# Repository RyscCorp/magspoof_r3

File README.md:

# Magspoof R3
[Rysc Corp](https://ryscc.com)

The [Magspoof R3](https://ryscc.com/products/magspoof) is based on the following prior works:

* https://github.com/samyk/magspoof
* https://github.com/salmg/MagSpoofPI

## Hardware Changes
* Integrated PCB coil
* Coin cell battery
* On/Off switch
* Programming header

## Firmware Changes
* Removed arduino dependencies
* Source code simplification
* Variable swipe speed and track playback speed (improved read reliability)

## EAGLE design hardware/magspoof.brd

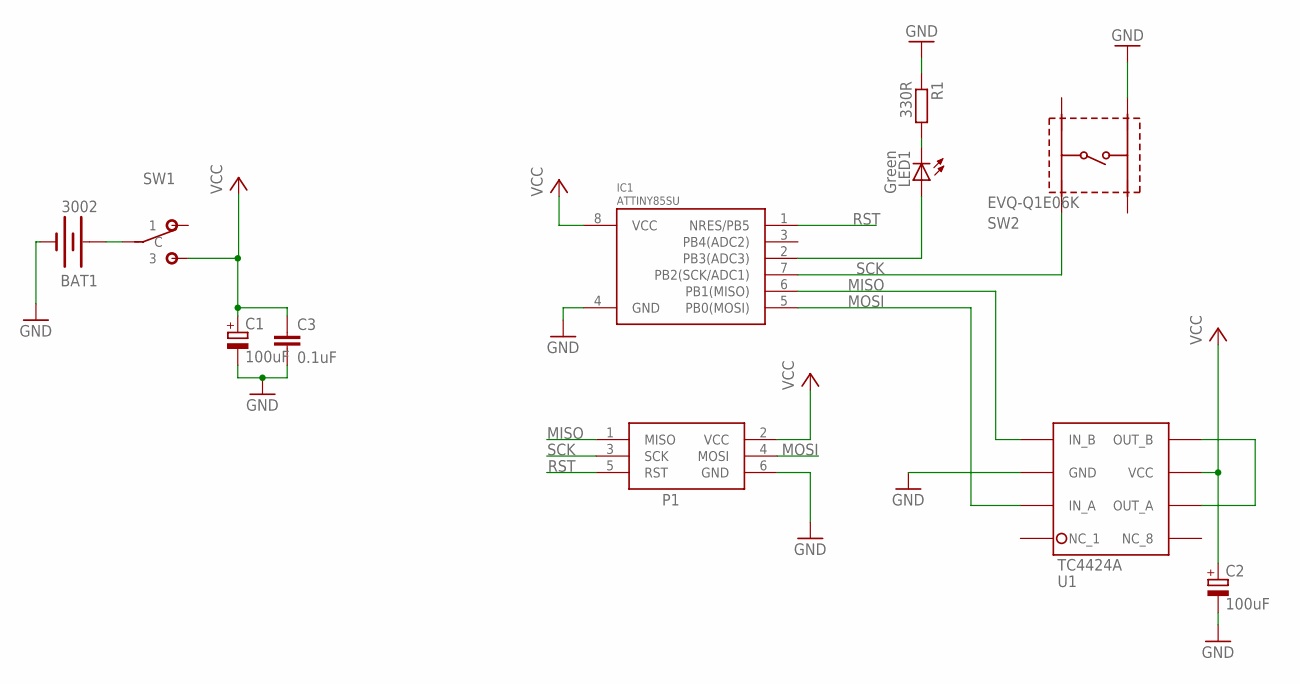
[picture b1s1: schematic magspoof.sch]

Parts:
BAT1: 3002; BATTCON_20MM
C1, C2: 100uF; C1411
C3: 0.1uF; C0603
IC1: ATTINY85SU; ATTINY85
LED1: Green; CHIPLED_0805
P1: AVRISP-6; AVRISP
R1: 330R; R0603
SW1: JS102011; JS102011SAQN
SW2: EVQ-Q1E06K; EVQQ1
U1: TC4424A; 8-SOIC

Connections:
ANTENNA: U1.5 (OUT_B), U1.7 (OUT_A)
GND: BAT1.-, C1.P$2 (-), C2.P$2 (-), C3.2, IC1.4 (GND), P1.6 (GND), R1.1, SW2.D, U1.3 (GND)
MISO: IC1.6 (PB1(MISO)), P1.1 (MISO), U1.4 (IN_B)
MOSI: IC1.5 (PB0(MOSI)), P1.4 (MOSI), U1.2 (IN_A)
unnamed: BAT1.+2 (+), SW1.P$2 (C)
unnamed: IC1.2 (PB3(ADC3)), LED1.A
unnamed: LED1.C, R1.2
RST: IC1.1 (NRES/PB5), P1.5 (RST)
SCK: IC1.7 (PB2(SCK/ADC1)), P1.3 (SCK), SW2.A
VCC: C1.P$1 (+), C2.P$1 (+), C3.1, IC1.8 (VCC), P1.2 (VCC), SW1.P$3 (3), U1.6 (VCC)

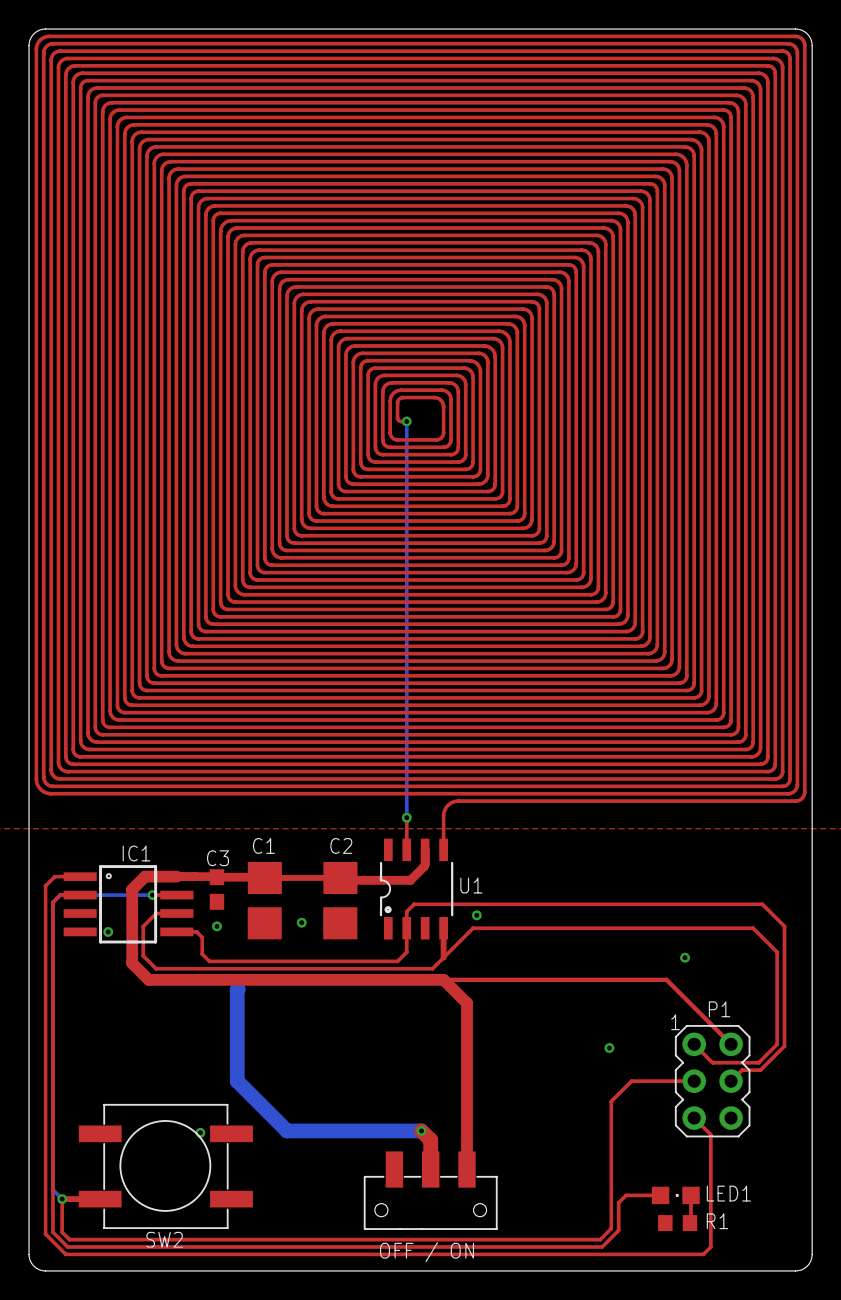
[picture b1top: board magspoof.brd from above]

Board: 2 copper layers, 54.0 x 85.6 mm, 11 parts (1 on the bottom side), 10 nets.

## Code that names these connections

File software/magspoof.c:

/*
 * MagSpoof - "wireless" magnetic stripe/credit card emulator
 *
 * Original by Samy Kamkar
 * MagSpoofPI by Salvador Mendoza
 *
 * http://samy.pl/magspoof
 * https://github.com/salmg/MagSpoofPI
 * https://netxing.wordpress.com/2016/08/27/magspoofpi/
 *
 */


#include <avr/io.h>
#include <util/delay.h>
#include <avr/interrupt.h>
#include <avr/sleep.h>

                            // min 5 IPS, max 50 IPS
#define SWIPE_SPEED   10    // inches per second

#define bool uint8_t
#define HIGH 1
#define LOW 0

#define interrupts() sei()
#define no_interrupts() cli()

/*
#define SINGLE_POLE   // only drive one side of the coil
                      // as described in http://www.idogendel.com/en/archives/507
*/

#define COIL_A PB0
#define COIL_B PB1
#define BUTTON_PIN PB2
#define LED_PIN PB3 
   
// I/O macros
#define PIN_HIGH(pin)   PORTB |= (HIGH << pin)
#define PIN_LOW(pin)    PORTB &= ~(HIGH << pin)
#define PINREAD(pin)    PINB & (HIGH << pin)

const uint16_t leading_zeros[3] = { 10, 20, 10 };
const uint16_t trailing_zeros[3] = { 10, 10, 10 };
const uint8_t track_density[3] = { 210, 75, 210 }; // bits per inch for each track
const uint8_t track_sublen[] = { 32, 48, 48 };
const uint8_t track_bitlen[] = { 7, 5, 5 };

uint32_t track_period_us[3];  // bit period of each track in microseconds
                              // initialized in calc_track_periods()

typedef struct {
  char *tracks[3];  // track data
} card;

// your magstripe card tracks go here
const card test_card = {
  {
    "%B4444444444444444^ABE/LINCOLN^291110100000931?",
    ";4444444444444444=29111010000093100000?",
    0
  },
};

void calc_track_periods()
{
  for (int i = 0; i < 3; i++)
    track_period_us[i] = (uint32_t) (1e6 / (SWIPE_SPEED * track_density[i]));
}

void static inline burn_cycles(uint32_t cycles)
{
  while (cycles > 0) {
    __asm__ volatile ("nop");
    cycles--;
  }
}

void static inline delay_us(uint32_t us)
{
  // obtained divisor of 20 by checking bit period with scope
  // assume loop in burn_cycles requires 20 clock cycles
  uint32_t cycles = (us * (F_CPU / 1000000)) / 20;
  burn_cycles(cycles);
}

void set_pin(uint8_t pin, bool state){
  if (state) {
    PORTB |= (1 << pin); // high
  }
  else {
    PORTB &= ~(1 << pin); // low
  }
}

void blink(int times)
{
  int i;
  for (i = 0; i < times; i++) {
    PIN_HIGH(LED_PIN);
    _delay_ms(200);
    PIN_LOW(LED_PIN);
    _delay_ms(200);
   } 
}

void setup_io()
{
  no_interrupts();

  DDRB |= (1 << COIL_A); // output
  DDRB |= (1 << COIL_B); // output
  DDRB |= (1 << LED_PIN); // output
  // DDRB = 0 by default so

  // BUTTON_PIN configured as input
  PORTB |= (1<<BUTTON_PIN); // set pull-up 
}

void await_button_press()
{
  while (PINREAD(BUTTON_PIN)) // button pin is high when not pressed
    _delay_ms(100);
}

static bool f2f_pole; // used to track signal state during playback (F2F encoding)

static inline void invert_coil_pole()
{
  f2f_pole ^= 1;
  set_pin(COIL_A, f2f_pole);
#ifndef SINGLE_POLE
  set_pin(COIL_B, !f2f_pole);
#endif
}

void f2f_play_bit(bool bit, uint32_t period_us)
{
  // play F2F encoded bit
  // see http://www.edn.com/Home/PrintView?contentItemId=4426351
  const uint32_t half_period = period_us / 2;
  // invert magnetic pole at start of period
  invert_coil_pole();

  delay_us(half_period);

  // at half period, determine whether to invert pole
  if (bit)
    invert_coil_pole();

  delay_us(half_period);
}

void play_zeros(uint8_t n, uint32_t period_us)
{
  for (int i = 0; i < n; i++)
    f2f_play_bit(0, period_us); 
}

void play_byte(
  uint8_t byte, 
  uint8_t n_bits, 
  uint32_t period_us,
  uint8_t *lrc
)
{
    bool parity = 1;
    for (int i = 0; i < n_bits; i++) {
      bool bit = byte & 1;
      parity ^= bit;
                                                // TIMING SENSITIVE
      f2f_play_bit(bit, period_us - 30);        // subtract 30us to compensate for delay 
                                                // caused by extra processing within this loop
      byte >>= 1;
      if (lrc)
        *lrc ^= bit << i;
    }
    f2f_play_bit(parity, period_us);  // last bit is parity
}

void play_track(card *c, uint8_t track_num)
{
  char *track = c->tracks[track_num];

  if (!track) return; // check that the track exists

  uint32_t period_us = track_period_us[track_num];
  char *track_byte;
  uint8_t lrc = 0;

  // lead playback with zeros
  play_zeros(leading_zeros[track_num], period_us);

  // play back track data
  for (track_byte = track; *track_byte != 0; track_byte++) {
    uint8_t tb = *track_byte - track_sublen[track_num];
    play_byte(tb, track_bitlen[track_num] - 1, period_us, &lrc);
  }

  // play LRC
  play_byte(lrc, track_bitlen[track_num] - 1, period_us, 0);

  // end playback
  play_zeros(trailing_zeros[track_num], period_us);
}

void play_card(card *c)
{
  // let user know playback has begun by turning on LED
  PIN_HIGH(LED_PIN);
  PIN_LOW(COIL_A);
  PIN_LOW(COIL_B);

  f2f_pole = 0;

  for (int i = 0; i < 3; i++)
    play_track(c, i);

  // turn off LED and make sure coils are off
  PIN_LOW(LED_PIN);
  PIN_LOW(COIL_A);
  PIN_LOW(COIL_B);
}

int main(void)
{
  setup_io();
  calc_track_periods();

  // blink three times to show we initialized
  blink(3);

  while (1) {
    await_button_press();
    play_card(&test_card);
  }
}

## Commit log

2017-04-24 Magspoof R3 Initial Commit
2017-04-24 Update README.md
    Fix link.
2017-04-25 Changed default programmer
    Changed default programmer from avrispmkII to usbtiny
2018-10-25 fixed typo: SINGLE_POL → SINGLE_POLE

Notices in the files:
parts and their libraries:
rysc: SEE LICENSE
